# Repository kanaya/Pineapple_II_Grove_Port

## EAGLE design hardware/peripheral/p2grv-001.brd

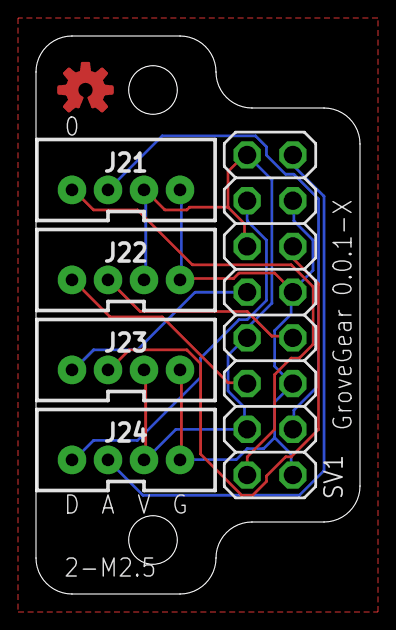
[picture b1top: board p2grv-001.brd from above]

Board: 2 copper layers, 18.0 x 31.0 mm, 7 parts (1 on the bottom side), 10 nets.

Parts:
J21, J22, J23, J24: JST-4-PTH-VERT
LOGO1: OSHW-LOGOS-COPPER; OSHW-LOGO-S_COPPER
SV1: 2X08
U$1: PINEAPPLE450_SILK

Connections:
ANLG0: J21.2, SV1.3
ANLG1: J22.2, SV1.7
ANLG2: J23.2, SV1.11
ANLG3: J24.2, SV1.15
DTCT0: J21.1, SV1.2
DTCT1: J22.1, SV1.6
DTCT2: J23.1, SV1.10
DTCT3: J24.1, SV1.14
GND: J21.4, J22.4, J23.4, J24.4, SV1.1, SV1.5, SV1.9, SV1.13
VCC: J21.3, J22.3, J23.3, J24.3, SV1.4, SV1.8, SV1.12, SV1.16

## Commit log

2022-08-16 Imported from RLY Port 0.0.2-X.
2022-08-17 Imported (again) from Hex Sw 0.0.2-X.
2022-08-17 WIP.
2022-08-17 Initial design.
2022-08-17 Silk and GND pattern.
2022-08-17 Parts number.
2022-08-17 Silk.

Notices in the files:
parts and their libraries:
SparkFun-Aesthetics: Licensing: Creative Commons ShareAlike 4.0 International - https://creativecommons.org/licenses/by-sa/4.0
